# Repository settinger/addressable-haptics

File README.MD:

# Addressable Haptics

This project aims to make it easy to control long strings of haptic motors (or regular motors, or just about anything) from an Arduino or similar microcontroller. By decentralizing the motor control systems, daisy-chaining the motors and relying on one-wire communication, we drastically cut down on the number of PWM output pins needed.

This project and README are works-in-progress. Expect lots of changes.

## About the circuit

Each motor is accompanied by an ATtiny10 microcontroller that handles the reception, transmission, and decoding of commands. When a valid command is read, the ATtiny10 sets the motor intensity by PWMing an N-channel MOSFET. The ATtiny10 will continue to drive the motor while receiving and transmitting additional commands.

## About the communication protocol

Each chain of motors communicates using one wire, similar to the WS2812 LED system. Unlike the WS2812 LEDs, these motors are controlled individually, without a shift register. I felt that a shift register protocol would not be as useful for haptic motor applications, so I did not implement it.

The coding scheme is simple but I don't know the name for it. A one bit is encoded as LOW for 20 μs, then HIGH for 180 μs. A zero bit is encoded as LOW for 150 μs, then HIGH for 50 μs. When not transferring information, the line is usually HIGH. The actual timing of the bits may change as I continue development, so watch out!

Motors are given unary addresses. The first motor is address _0_, the second is address _10_, the third is _110_, the fourth is _1110_, the _n_th is (_n_-1) 1s followed by a 0. This allows the motor controllers to pass commands down the chain with less latency; however, it creates a strong disincentive for long chains of motors.

Each command is of the form `<address><value>`. The `value` is a 7-bit number that sets the PWM duty cycle for the motor at `address`. So, for example, the command `11101010101` would set motor #4 (that is, the motor with address `1110`) to an intensity of `1010101`, or 85/127.

## Some more detail about the communication protocol

If the first ATtiny10 receives a command that starts with `0`, it knows instantly that the message is intended for it. Similarly, if the first ATtiny10 receives a command that starts with `1`, it knows to pass the message down the line. However, it transmits the message _without the initial bit_. That is, if an ATtiny10 receives the command `101111111`, it would pass along the message `01111111`. This informs the next ATtiny10 in the chain that the command is intended for it.

## Why not just use WS2811 ICs?

1. I wanted to implement my own protocol and learn from the process.
1. I don't know the PWM frequency of the WS2811 and can't change it to suit inductive loads.
1. The shift-register approach doesn't make sense for the applications I envision.
1. I just enjoy using ATtiny10s!

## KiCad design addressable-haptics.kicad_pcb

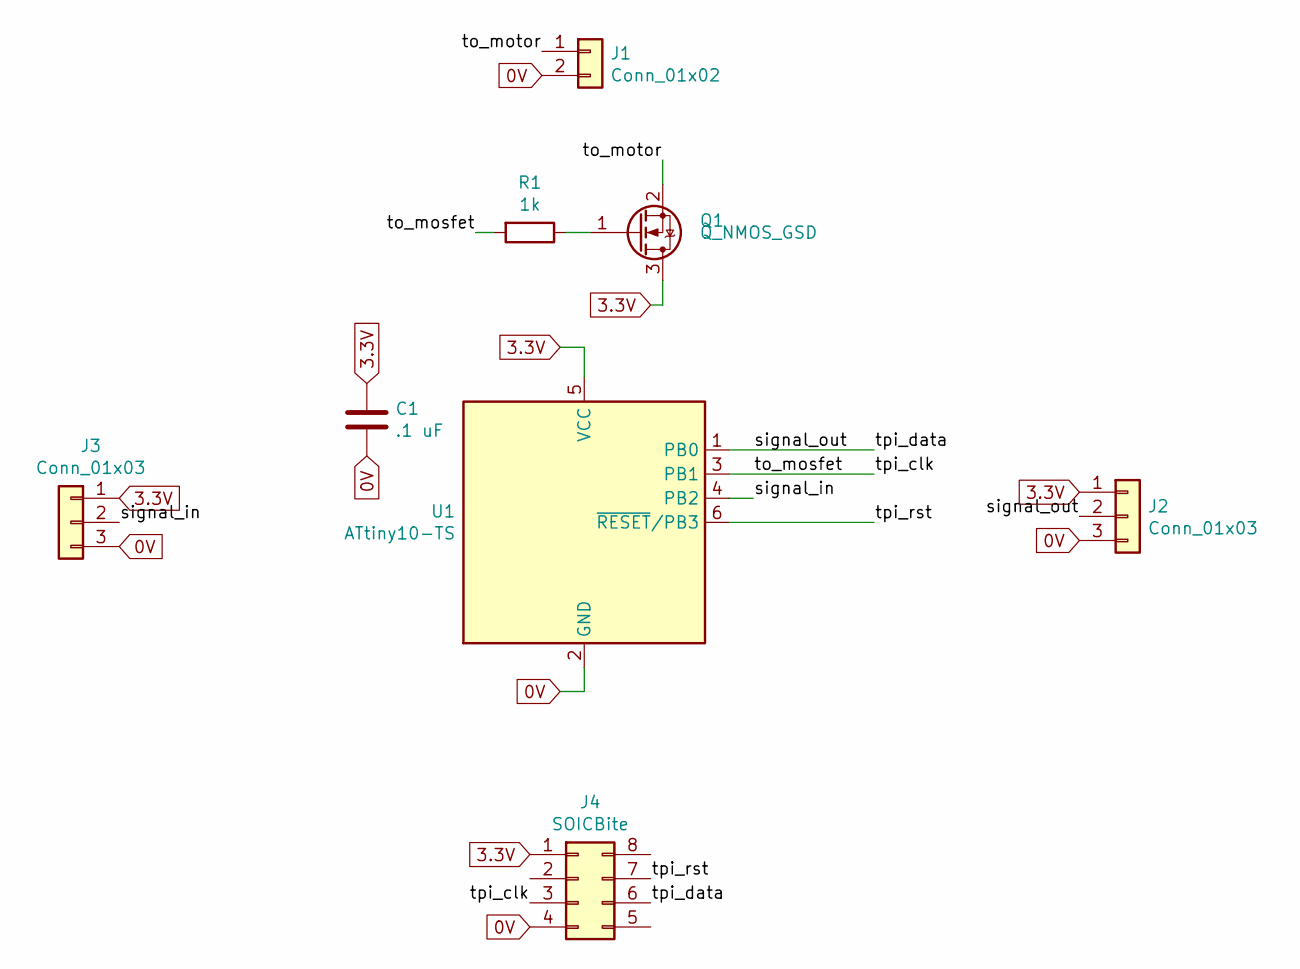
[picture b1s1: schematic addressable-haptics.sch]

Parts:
C1: .1 uF; C_0805_2012Metric
J1: Conn_01x02; PinSocket_1x02_P2.54mm_Vertical
J2: Conn_01x03; PinSocket_1x03_P2.54mm_Horizontal
J3: Conn_01x03; PinHeader_1x03_P2.54mm_Horizontal
J4: SOICBite; SOIC_clipProgSmall
Q1: Q_NMOS_GSD; SOT-23
R1: 1k; R_0805_2012Metric
U1: ATtiny10-TS; SOT-23-6

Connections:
0V: C1.2, J1.2, J2.3, J3.3, J4.4, U1.2 (GND)
3.3V: C1.1, J2.1, J3.1, J4.1, Q1.3 (D), U1.5 (VCC)
/signal_in: J3.2, U1.4 (PB2)
/signal_out: J2.2, J4.6, U1.1 (PB0)
/to_mosfet: J4.3, R1.2, U1.3 (PB1)
/to_motor: J1.1, Q1.2 (S)
/tpi_rst: J4.7, U1.6 (~RESET~/PB3)
unnamed: Q1.1 (G), R1.1

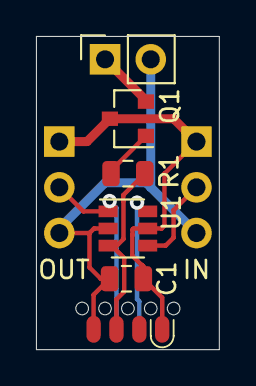
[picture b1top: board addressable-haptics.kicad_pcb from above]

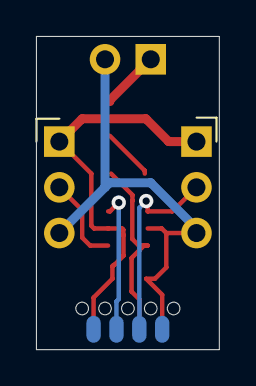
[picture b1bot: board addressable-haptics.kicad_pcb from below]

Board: 2 copper layers, 10.2 x 17.4 mm, 8 parts (2 on the bottom side), 8 nets.

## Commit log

2020-02-19 First pass at firmware
2020-02-19 Added a bit more
2020-02-19 Fixed interrupt startup
2020-08-19 Updates now that I have hardware to test
2020-08-21 Updated firmware and software
2020-08-21 Update PCB
2020-08-27 Fixed schematic
2020-08-27 added readme
2020-09-18 Sped up instructions
